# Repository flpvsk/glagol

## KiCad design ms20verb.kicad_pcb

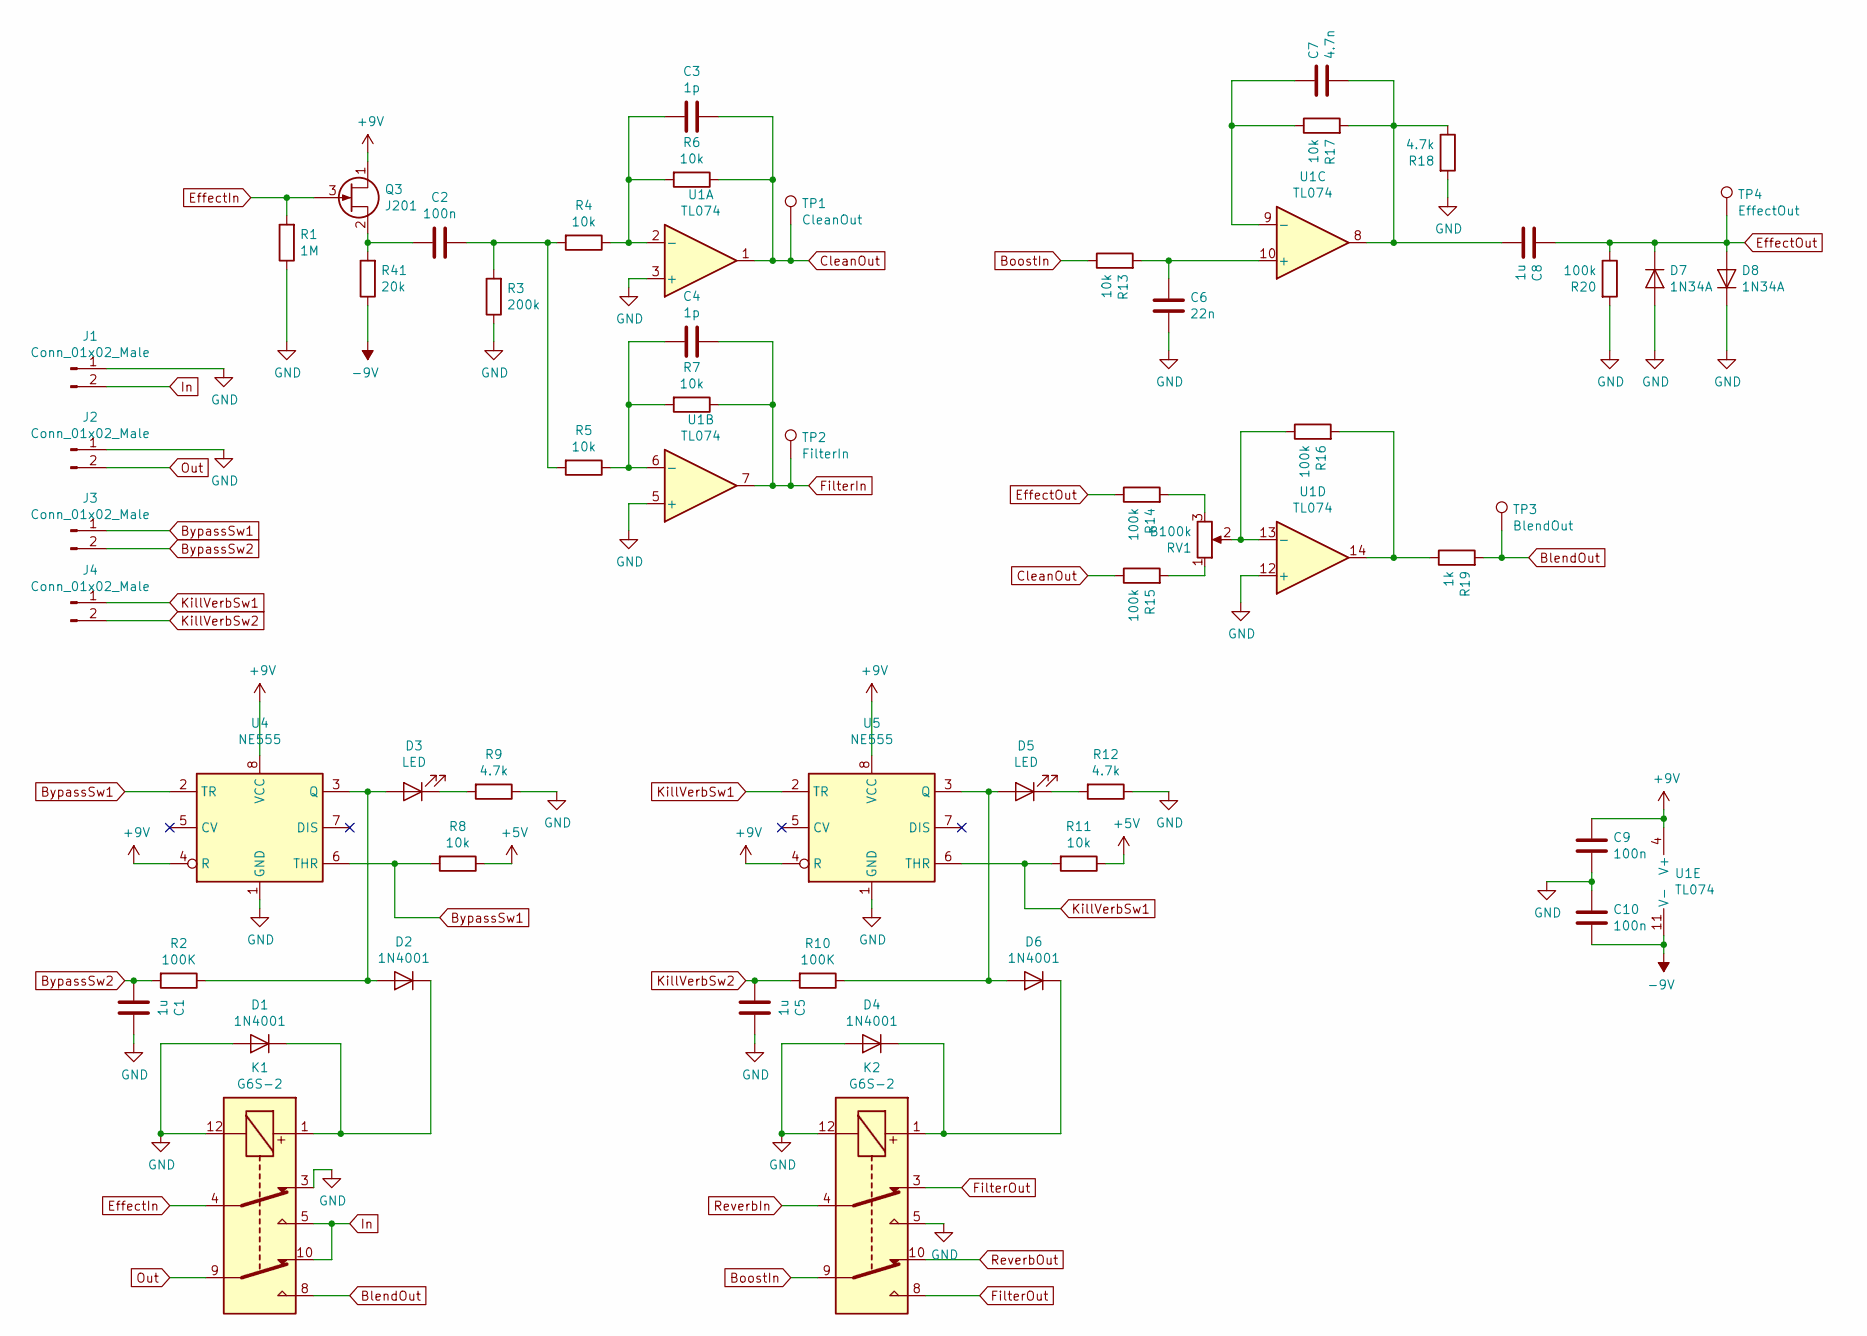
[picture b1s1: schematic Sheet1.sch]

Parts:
C1, C5, C8: 1u; C_Rect_L7.0mm_W4.5mm_P5.00mm
C2, C9, C10: 100n; C_Rect_L7.0mm_W2.5mm_P5.00mm
C3, C4: 1p; C_Disc_D4.7mm_W2.5mm_P5.00mm
C6: 22n; C_Disc_D5.1mm_W3.2mm_P5.00mm
C7: 4.7n; C_Disc_D5.1mm_W3.2mm_P5.00mm
D1, D2, D4, D6: 1N4001; D_DO-41_SOD81_P10.16mm_Horizontal
D3, D5: LED; LED_D5.0mm
D7, D8: 1N34A; D_DO-41_SOD81_P10.16mm_Horizontal
J1, J2, J3, J4: Conn_01x02_Male; JST_XH_B2B-XH-A_1x02_P2.50mm_Vertical
K1, K2: G6S-2; 8-PIN_Fujitsu_Tayda
Q3: J201; TO-92L_Inline_Wide
R1: 1M; R_0603_1608Metric
R2, R10: 100K; R_0603_1608Metric
R3: 200k; R_0603_1608Metric
R4, R5, R6, R7, R8, R11, R13, R17: 10k; R_0603_1608Metric
R9, R12, R18: 4.7k; R_0603_1608Metric
R14, R15, R16, R20: 100k; R_0603_1608Metric
R19: 1k; R_0603_1608Metric
R41: 20k; R_0603_1608Metric
RV1: B100k; 16MM_B.MOUNT_BANZAI
TP1: CleanOut; TestPoint_THTPad_D1.5mm_Drill0.7mm
TP2: FilterIn; TestPoint_THTPad_D1.5mm_Drill0.7mm
TP3: BlendOut; TestPoint_THTPad_D1.5mm_Drill0.7mm
TP4: EffectOut; TestPoint_THTPad_D1.5mm_Drill0.7mm
U1: TL074; DIP-14_W7.62mm
U4, U5: NE555; DIP-8_W7.62mm

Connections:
+5V: R8.1, R11.1; also elsewhere on the board
+9V: C9.1, Q3.1 (D), U1.4 (V+), U4.4 (R), U4.8 (VCC), U5.4 (R), U5.8 (VCC); also elsewhere on the board
-9V: C10.2, R41.1, U1.11 (V-); also elsewhere on the board
BlendOut: K1.8, R19.2, TP3.1
BoostIn: K2.9, R13.1
BypassSw1: J3.1, R8.2, U4.2 (TR), U4.6 (THR)
BypassSw2: C1.2, J3.2, R2.2
CleanOut: C3.1, R6.1, R15.1, TP1.1, U1.1
EffectIn: K1.4, Q3.3 (G), R1.2
EffectOut: C8.2, D7.1 (K), D8.2 (A), R14.1, R20.1, TP4.1
FilterIn: C4.1, R7.1, TP2.1, U1.7; also elsewhere on the board
FilterOut: K2.3, K2.8; also elsewhere on the board
GND: C1.1, C5.1, C6.1, C9.2, C10.1, D1.2 (A), D4.2 (A), D7.2 (A), D8.1 (K), J1.1, J2.1, K1.3, K1.12, K2.5, K2.12, R1.1, R3.1, R9.1, R12.1, R18.2, R20.2, U1.3 (+), U1.5 (+), U1.12 (+), U4.1 (GND), U5.1 (GND); also elsewhere on the board
In: J1.2, K1.5, K1.10
KillVerbSw1: J4.1, R11.2, U5.2 (TR), U5.6 (THR)
KillVerbSw2: C5.2, J4.2, R10.2
unnamed: C2.1, R3.2, R4.2, R5.2
unnamed: C2.2, Q3.2 (S), R41.2
unnamed: C3.2, R4.1, R6.2, U1.2 (-)
unnamed: C4.2, R5.1, R7.2, U1.6 (-)
unnamed: C6.2, R13.2, U1.10 (+)
unnamed: C7.1, C8.1, R17.2, R18.1, U1.8
unnamed: C7.2, R17.1, U1.9 (-)
unnamed: D1.1 (K), D2.1 (K), K1.1
unnamed: D2.2 (A), D3.2 (A), R2.1, U4.3 (Q)
unnamed: D3.1 (K), R9.2
unnamed: D4.1 (K), D6.1 (K), K2.1
unnamed: D5.1 (K), R12.2
unnamed: D5.2 (A), D6.2 (A), R10.1, U5.3 (Q)
unnamed: R14.2, RV1.3
unnamed: R15.2, RV1.1
unnamed: R16.1, RV1.2, U1.13 (-)
unnamed: R16.2, R19.1, U1.14
Out: J2.2, K1.9
ReverbIn: K2.4; also elsewhere on the board
ReverbOut: K2.10; also elsewhere on the board

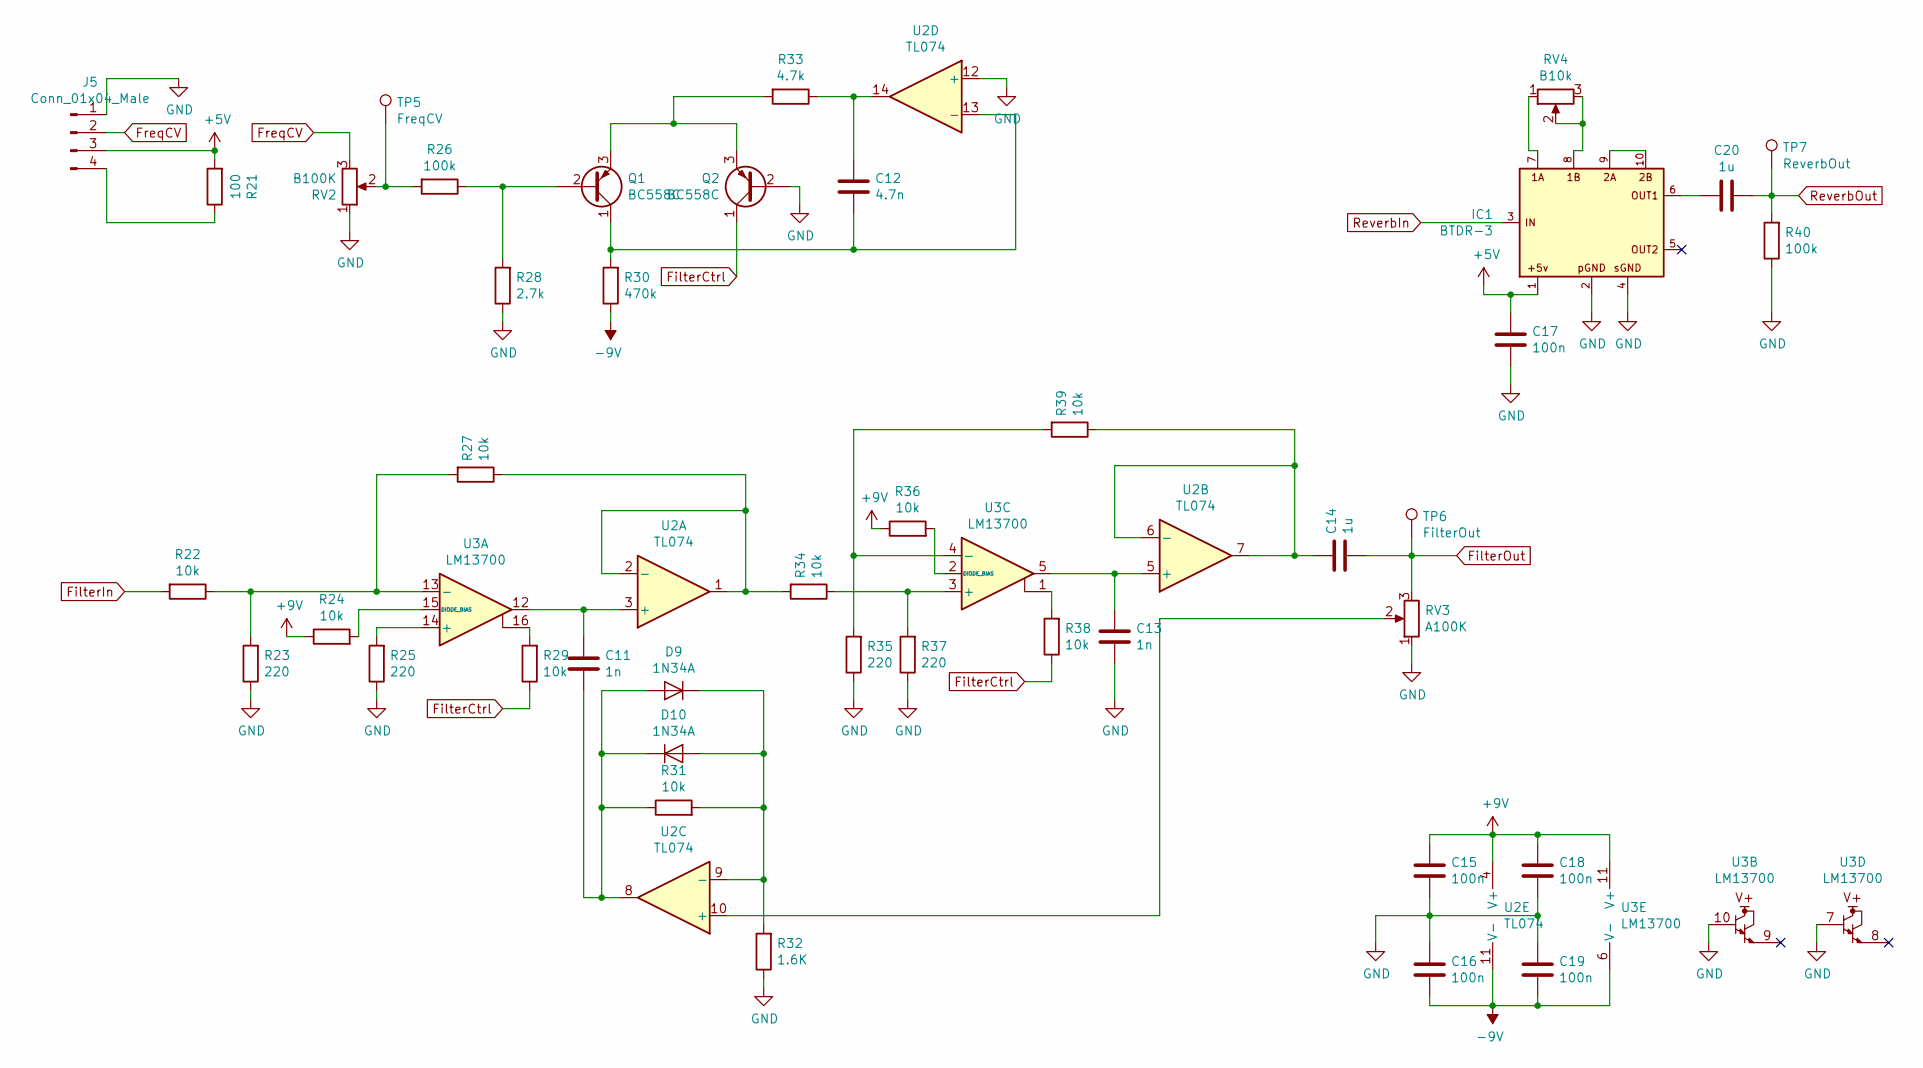
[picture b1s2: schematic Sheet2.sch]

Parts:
C11, C13: 1n; C_Disc_D5.1mm_W3.2mm_P5.00mm
C12: 4.7n; C_Disc_D5.1mm_W3.2mm_P5.00mm
C14, C20: 1u; C_Rect_L7.0mm_W4.5mm_P5.00mm
C15, C16, C17, C18, C19: 100n; C_Rect_L7.0mm_W2.5mm_P5.00mm
D9, D10: 1N34A; D_DO-41_SOD81_P10.16mm_Horizontal
IC1: BTDR-3
J5: Conn_01x04_Male; JST_XH_B4B-XH-A_1x04_P2.50mm_Vertical
Q1, Q2: BC558C; TO-92L_Inline_Wide
R21: 100; R_0603_1608Metric
R22, R24, R27, R29, R31, R34, R36, R38, R39: 10k; R_0603_1608Metric
R23, R25, R35, R37: 220; R_0603_1608Metric
R26, R40: 100k; R_0603_1608Metric
R28: 2.7k; R_0603_1608Metric
R30: 470k; R_0603_1608Metric
R32: 1.6K; R_0603_1608Metric
R33: 4.7k; R_0603_1608Metric
RV2: B100K; 16MM_B.MOUNT_BANZAI
RV3: A100K; 16MM_B.MOUNT_BANZAI
RV4: B10k; 16MM_B.MOUNT_BANZAI
TP5: FreqCV; TestPoint_THTPad_D1.5mm_Drill0.7mm
TP6: FilterOut; TestPoint_THTPad_D1.5mm_Drill0.7mm
TP7: ReverbOut; TestPoint_THTPad_D1.5mm_Drill0.7mm
U2: TL074; DIP-14_W7.62mm
U3: LM13700; DIP-16_W7.62mm

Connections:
+5V: C17.1, IC1.1, J5.3, R21.2; also elsewhere on the board
+9V: C15.1, C18.1, R24.1, R36.1, U2.4 (V+), U3.11 (V+); also elsewhere on the board
-9V: C16.2, C19.2, R30.1, U2.11 (V-), U3.6 (V-); also elsewhere on the board
FilterCtrl: Q2.1 (C), R29.1, R38.1
FilterIn: R22.2; also elsewhere on the board
FilterOut: C14.1, RV3.3, TP6.1; also elsewhere on the board
FreqCV: J5.2, RV2.3
GND: C13.1, C15.2, C16.1, C17.2, C18.2, C19.1, IC1.2, IC1.4, J5.1, Q2.2 (B), R23.1, R25.1, R28.1, R32.1, R35.1, R37.1, R40.1, RV2.1, RV3.1, U2.12 (+), U3.7, U3.10; also elsewhere on the board
unnamed: C11.1, D9.2 (A), D10.1 (K), R31.1, U2.8
unnamed: C11.2, U2.3 (+), U3.12
unnamed: C12.1, Q1.1 (C), R30.2, U2.13 (-)
unnamed: C12.2, R33.1, U2.14
unnamed: C13.2, U2.5 (+), U3.5
unnamed: C14.2, R39.1, U2.6 (-), U2.7
unnamed: C20.2, IC1.6
unnamed: D9.1 (K), D10.2 (A), R31.2, R32.2, U2.9 (-)
unnamed: IC1.7, RV4.1
unnamed: IC1.8, RV4.2, RV4.3
unnamed: IC1.9, IC1.10
unnamed: J5.4, R21.1
unnamed: Q1.2 (B), R26.1, R28.2
unnamed: Q1.3 (E), Q2.3 (E), R33.2
unnamed: R22.1, R23.2, R27.2, U3.13 (-)
unnamed: R24.2, U3.15 (DIODE_BIAS)
unnamed: R25.2, U3.14 (+)
unnamed: R26.2, RV2.2, TP5.1
unnamed: R27.1, R34.2, U2.1, U2.2 (-)
unnamed: R29.2, U3.16
unnamed: R34.1, R37.2, U3.3 (+)
unnamed: R35.2, R39.2, U3.4 (-)
unnamed: R36.2, U3.2 (DIODE_BIAS)
unnamed: R38.2, U3.1
unnamed: RV3.2, U2.10 (+)
ReverbIn: IC1.3; also elsewhere on the board
ReverbOut: C20.1, R40.2, TP7.1; also elsewhere on the board

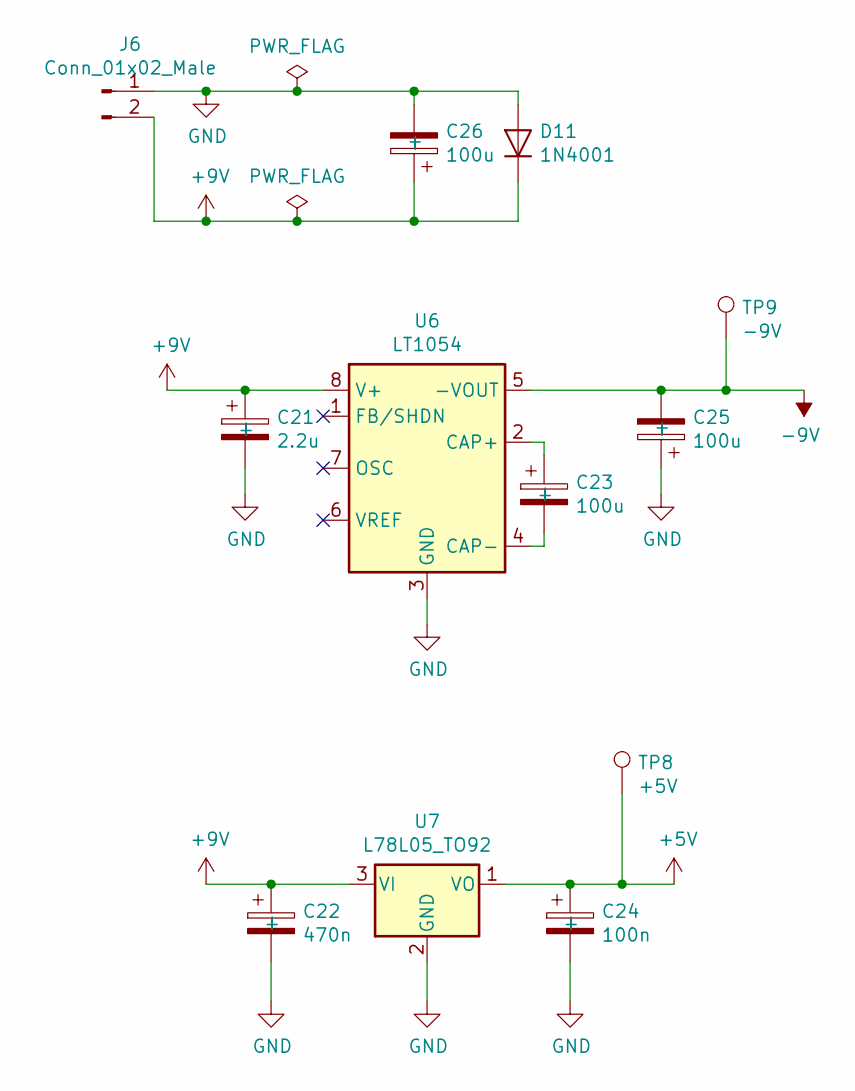
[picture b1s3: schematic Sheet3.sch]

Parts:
C21: 2.2u; CP_Radial_D5.0mm_P2.00mm
C22: 470n; CP_Radial_D5.0mm_P2.00mm
C23, C25, C26: 100u; CP_Radial_D5.0mm_P2.50mm
C24: 100n; CP_Radial_D5.0mm_P2.00mm
D11: 1N4001; D_DO-41_SOD81_P10.16mm_Horizontal
J6: Conn_01x02_Male; JST_XH_B2B-XH-A_1x02_P2.50mm_Vertical
TP8: +5V; TestPoint_THTPad_D1.5mm_Drill0.7mm
TP9: -9V; TestPoint_THTPad_D1.5mm_Drill0.7mm
U6: LT1054; DIP-8_W7.62mm
U7: L78L05_TO92; TO-92_Inline

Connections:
+5V: C24.1 (+), TP8.1, U7.1 (VO); also elsewhere on the board
+9V: C21.1 (+), C22.1 (+), C26.1 (+), D11.1 (K), J6.2, U6.8 (V+), U7.3 (VI); also elsewhere on the board
-9V: C25.2 (-), TP9.1, U6.5 (-VOUT); also elsewhere on the board
GND: C21.2 (-), C22.2 (-), C24.2 (-), C25.1 (+), C26.2 (-), D11.2 (A), J6.1, U6.3 (GND), U7.2 (GND); also elsewhere on the board
unnamed: C23.1 (+), U6.2 (CAP+)
unnamed: C23.2 (-), U6.4 (CAP-)

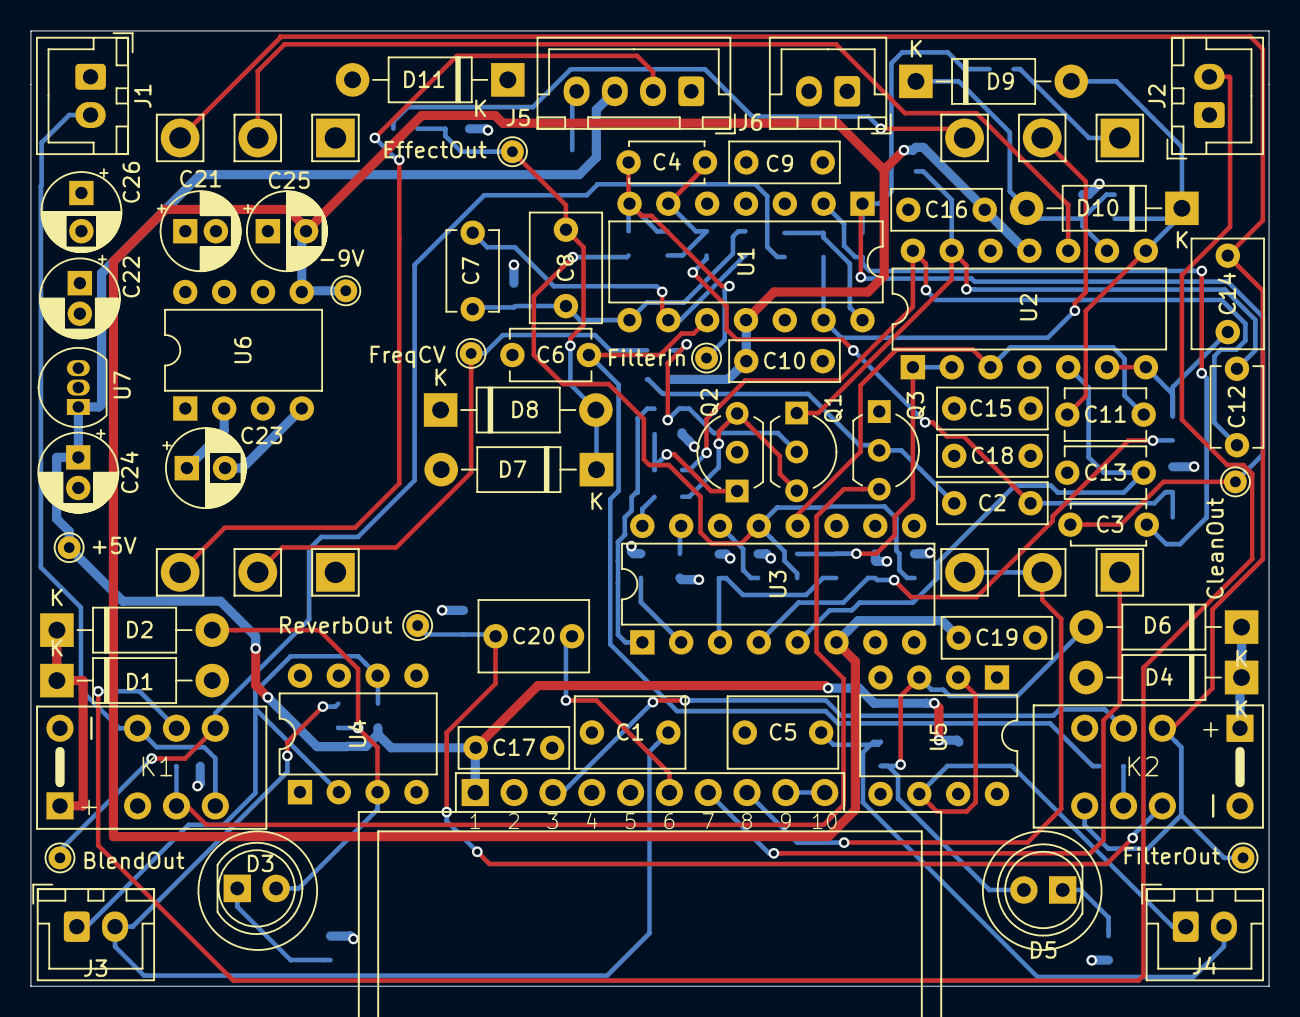
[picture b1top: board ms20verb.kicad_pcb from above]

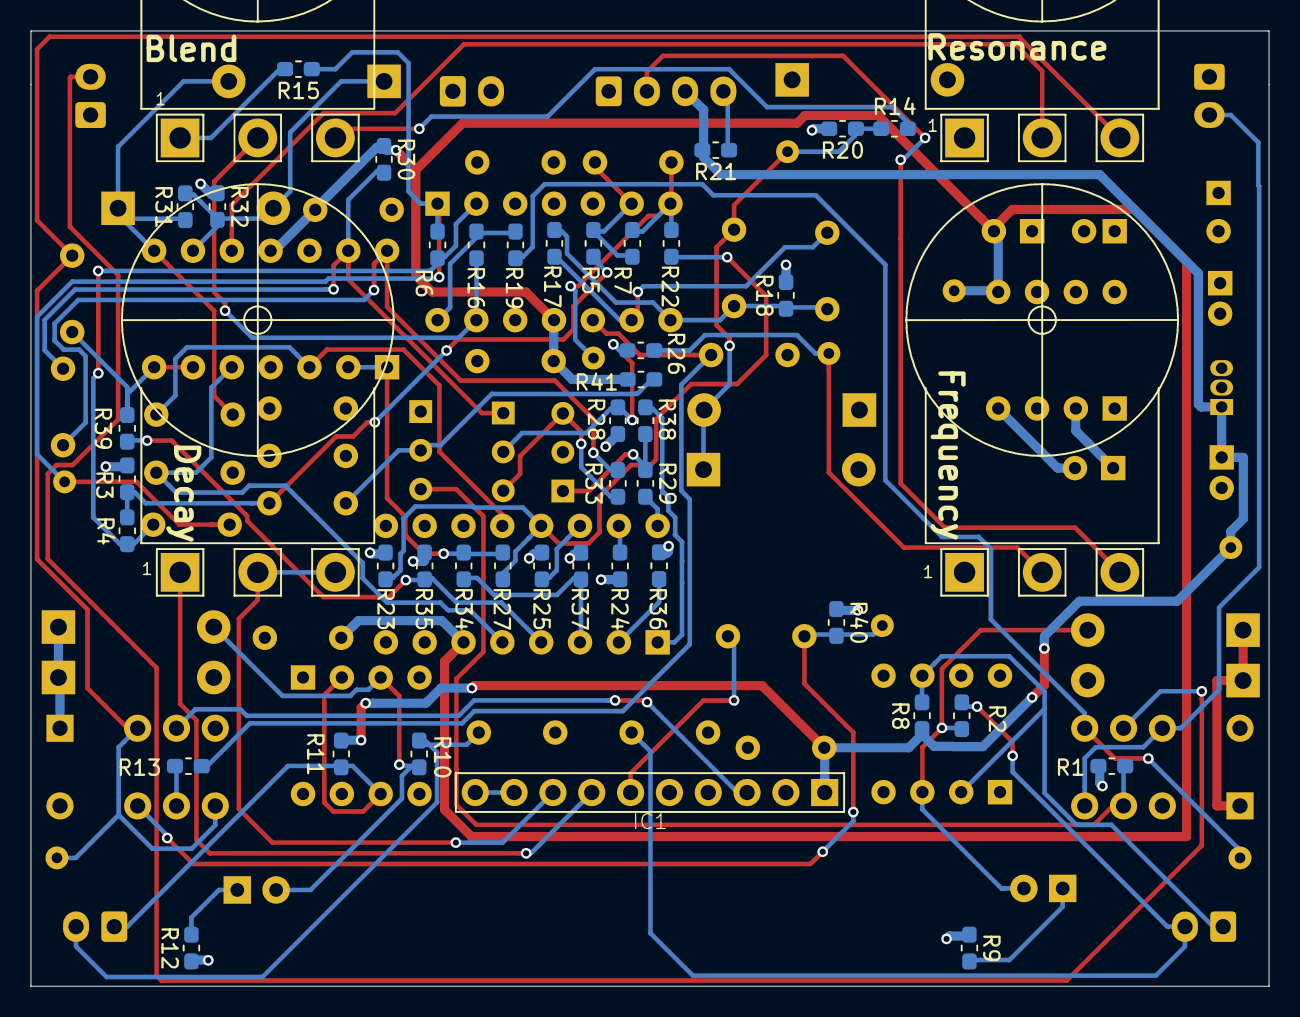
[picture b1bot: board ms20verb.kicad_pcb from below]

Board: 4 copper layers, 81.0 x 62.5 mm, 113 parts (41 on the bottom side), 65 nets.

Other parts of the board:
Ref**: Val**; MOMENTARY
Ref**#2: Val**; MOMENTARY
Ref**#3: Val**; DC_TOP

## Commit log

2021-08-14 TH version
2021-08-14 Resistors to SMD
2021-08-19 2 layer dead end
2021-08-19 4-layer board finished
2021-08-22 Hand-solder 0603 resistors
2021-09-10 v1 sent to JLC
2021-09-14 Pedal
